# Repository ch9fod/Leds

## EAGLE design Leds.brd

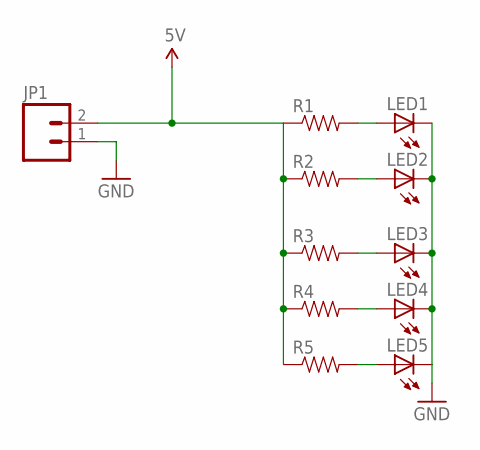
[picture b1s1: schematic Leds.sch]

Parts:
JP1: M02LOCK_LONGPADS; 1X02_LOCK_LONGPADS
LED1, LED2, LED3, LED4, LED5: LED5MM
R1, R2, R3, R4, R5: RESISTOR0805-RES; 0805

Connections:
5V: JP1.2, R1.1, R2.1, R3.1, R4.1, R5.1
GND: JP1.1, LED1.K (C), LED2.K (C), LED3.K (C), LED4.K (C), LED5.K (C)
unnamed: LED1.A, R1.2
unnamed: LED2.A, R2.2
unnamed: LED3.A, R3.2
unnamed: LED4.A, R4.2
unnamed: LED5.A, R5.2

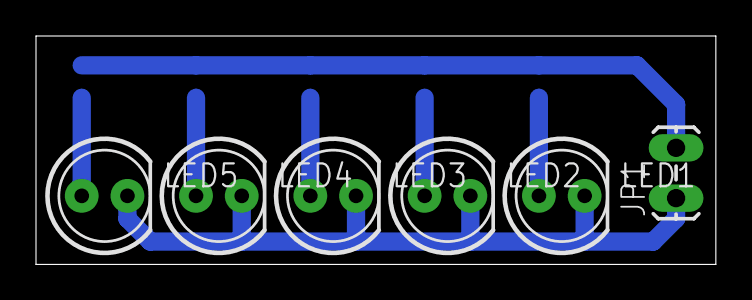
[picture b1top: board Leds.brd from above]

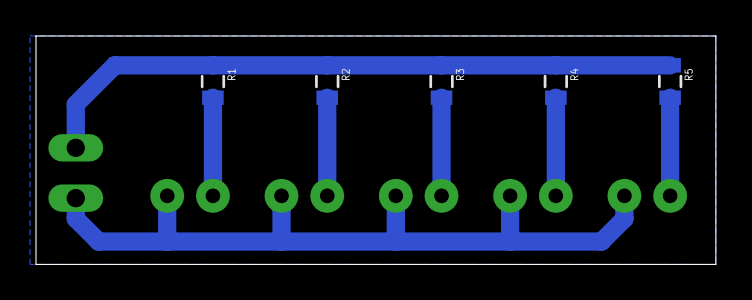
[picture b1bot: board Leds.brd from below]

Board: 2 copper layers, 37.8 x 12.7 mm, 11 parts (5 on the bottom side), 7 nets.

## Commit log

2012-12-10 5 bright leds

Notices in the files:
parts and their libraries:
SparkFun-Connectors: Licensing: CC v3.0 Share-Alike You are welcome to use this library for commercial purposes.
